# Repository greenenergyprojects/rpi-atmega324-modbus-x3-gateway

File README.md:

# rpi-atmega324-modbus-x3-gateway

This project implements a Modbus Gateway.  

The device is a gateway between Modbus-TCP (via TCP/IP on Raspberry) to Modbus-RTU (RS-485).
Modbus-TCP frames are send via the Raspberry UART interface (115200 Bit/s) to one microcontroller as Modbus-ASCII frame.
The microcontroller converts the Modbus-ASCII to Modbus-RTU frame and is handling all real time needs of the
Modbus-RTU standard. Frames for the other two Modbus interfaces are send via SPI interface to the second microcontroller.

**Features:**

* 3 interfaces Modbus-RTU
* 2 Microcontrollers (Atmgea324P)
* Raspberry PI
* For DIN-rail housing [Camdenboss CBRPP-DR-CLR](https://www.camdenboss.com/camden-boss/cbrpi-dr-2-3-clr-pi-b%2c-p2%2c-p3-din-rail-enclosure/c-23/p-16101)  
(W x H x D = 88mm x 90mm x 58mm; 4.8 DIN rails units)

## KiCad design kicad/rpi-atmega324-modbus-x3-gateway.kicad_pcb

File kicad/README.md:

# Manufacturing report

## Gerber Files

See [https://support.jlcpcb.com/article/44-how-to-export-kicad-pcb-to-gerber-files](https://support.jlcpcb.com/article/44-how-to-export-kicad-pcb-to-gerber-files)

# Bugs / Improvements

| Reference | Description |
| --------- | ----------- |
|           |             |

# Software

## Atmega324P Fuses

See [http://www.engbedded.com/fusecalc](http://www.engbedded.com/fusecalc)

* Ext crystal Osc, Frequ. 8.0- MHz, Startup 1K CK + 4.1ms
* Preserve EEPROM memory through Chip Erase cycle
* Serial program downloading enabled
* Brownout detection level 1.8V
* Watchdog disabled
* Boot flash size 1024 words, boot start 3c00 (=byte address 7800)
* Boot reset vector

```
avrdude -c usbasp -p atmega324p -U lfuse:w:0xfe:m -U hfuse:w:0xd2:m
avrdude -c usbasp -p atmega324p -U efuse:w:0xfe:m
```

## Bootloader

[https://www.htl-mechatronik.at/gitweb/public/sx/?p=Atmel-Bootloader.git;a=summary](https://www.htl-mechatronik.at/gitweb/public/sx/?p=Atmel-Bootloader.git;a=summary)

Download file [bootloader_atmega324p_115200_12MHz](https://www.htl-mechatronik.at/gitweb/public/sx/?p=Atmel-Bootloader.git;a=blob;f=bootloader_atmega324p/bootloader_atmega324p_115200_12MHz.hex)

avrdude -c usbasp -p atmega324p
avrdude -c usbasp -p atmega324p -e -U flash:w:bootloader_atmega324p_57600_12MHz.hex:i

## UART Baudrate

For the U1 microcontroller UART0 the baudrate 115200 Bit/s is recommended. This speed ensures a high data rate between RPI and microcontroller. Higher speeds are not possible with 12MHz system frequency.

Microcontroller: f = 12MHz		

|  Baudrate  |   Optimal UBRR0L  |     Error
|:----------:|:-----------------:| :-----------:
|     9600   |      155,25       |    0,0016
|    19200   |       77,12       |    0,0016
|    37400   |       39,11       |    0,0027
|    57600   |       25,04       |    0,0017
| **115200** |     **12,02**     |  **0,0017**
|   230400   |        5,51       |   -0,0888
|   560800   |        1,67       |   -0,1942

## Raspberry serial

Disable serial interface for Terminal with the tool `raspi-config`. Select `5 Interfacing Options` -> `P6 Serial` and select `NO`. Reboot is needed if the configuration has changed.

In the raspberry PI3 default configuration the Uart is used for Bluetooth communication. To allow serial port communcation via pin Txd (GPIO10) and Rxd (GPIO12)  a configuration change is necessary.

Edit the file`/boot/config.txt` and set the last lines to

```
enable_uart=1
core_freq=250
```

After reboot you can use `/dev/serial0` for serial communication between microcontroller and Raspberry. It depends on the raspberry version if `/dev/serial0` is a link to `/dev/ttyAMA0` (older raspberry) or `dev/ttyS0` (newer raspberry).

For more information:  
[http://www.netzmafia.de/skripten/hardware/RasPi/RasPi_Serial.html](http://www.netzmafia.de/skripten/hardware/RasPi/RasPi_Serial.html)

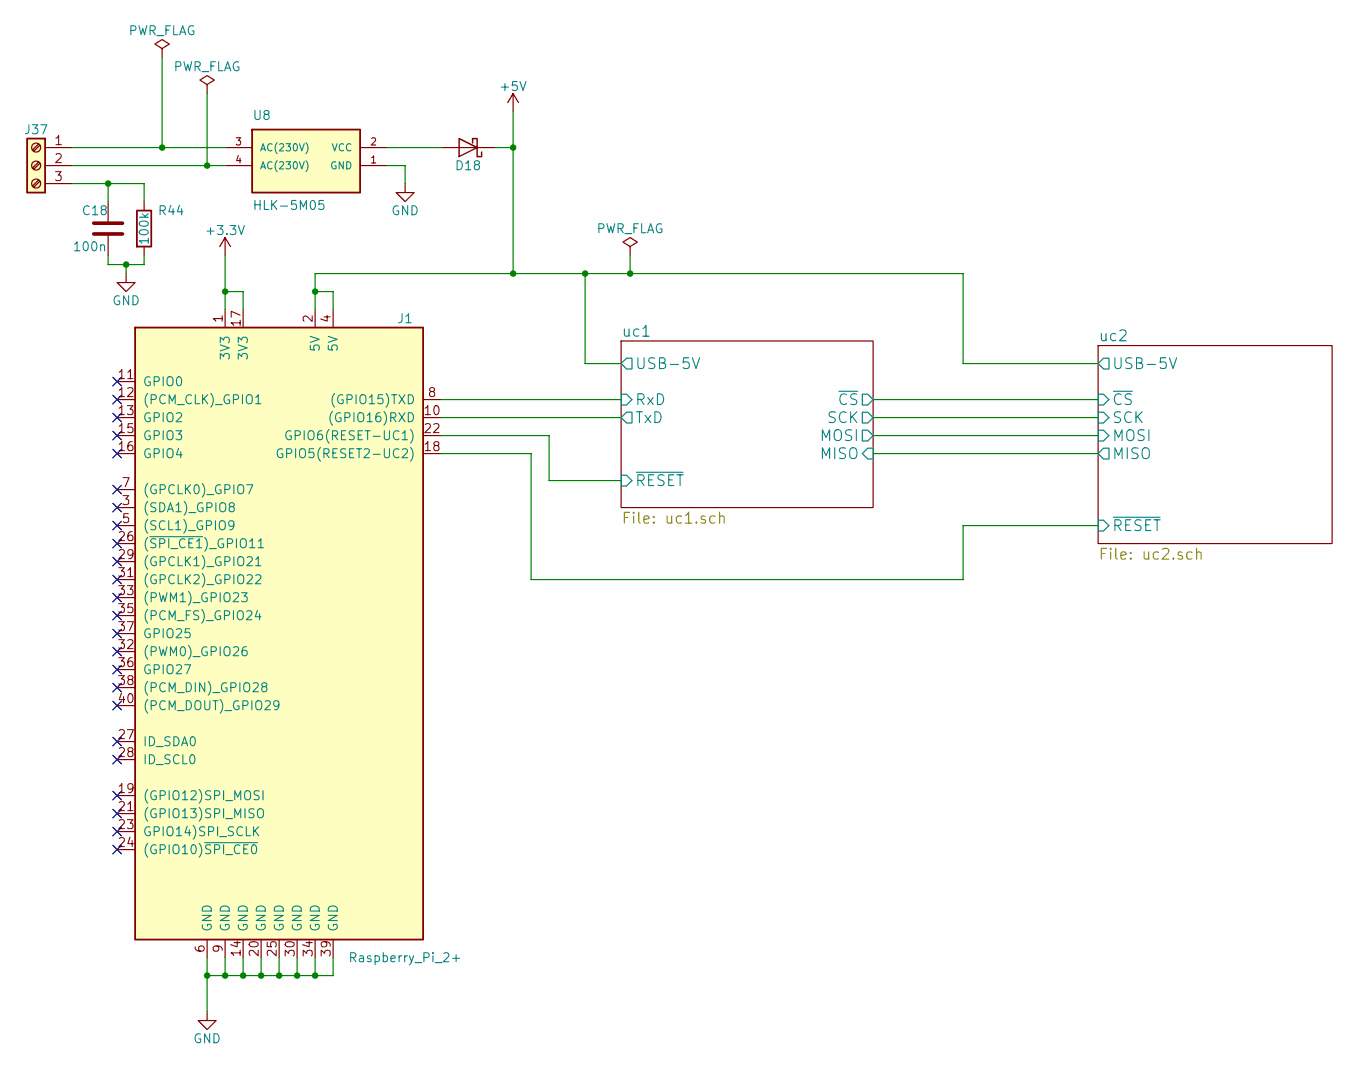
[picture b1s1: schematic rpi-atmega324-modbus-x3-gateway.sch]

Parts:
C18: 100n; C_1206_HandSoldering
D18: D_Schottky; D_2114
J1: Raspberry_Pi_2+; Raspberry-PI
J37: Screw_Terminal_01x03; Terminalblock-3x-5mm
R44: 100k; R_1206_HandSoldering
U8: HLK-5M05; HLK_5M05

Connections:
+3V3: J1.1 (3V3), J1.17 (3V3); also elsewhere on the board
+5V: D18.1 (K), J1.2 (5V), J1.4 (5V); also elsewhere on the board
/uc1/RxD: J1.8 ((GPIO15)TXD); also elsewhere on the board
/uc1/TxD: J1.10 ((GPIO16)RXD); also elsewhere on the board
/uc1/~RESET~: J1.22 (GPIO6(RESET-UC1)); also elsewhere on the board
/uc2/~RESET~: J1.18 (GPIO5(RESET2-UC2)); also elsewhere on the board
GND: C18.2, J1.6 (GND), J1.9 (GND), J1.14 (GND), J1.20 (GND), J1.25 (GND), J1.30 (GND), J1.34 (GND), J1.39 (GND), R44.2, U8.1 (GND); also elsewhere on the board
unnamed: C18.1, J37.3, R44.1
unnamed: D18.2 (A), U8.2 (VCC)
unnamed: J37.1, U8.3 (AC(230V))
unnamed: J37.2, U8.4 (AC(230V))

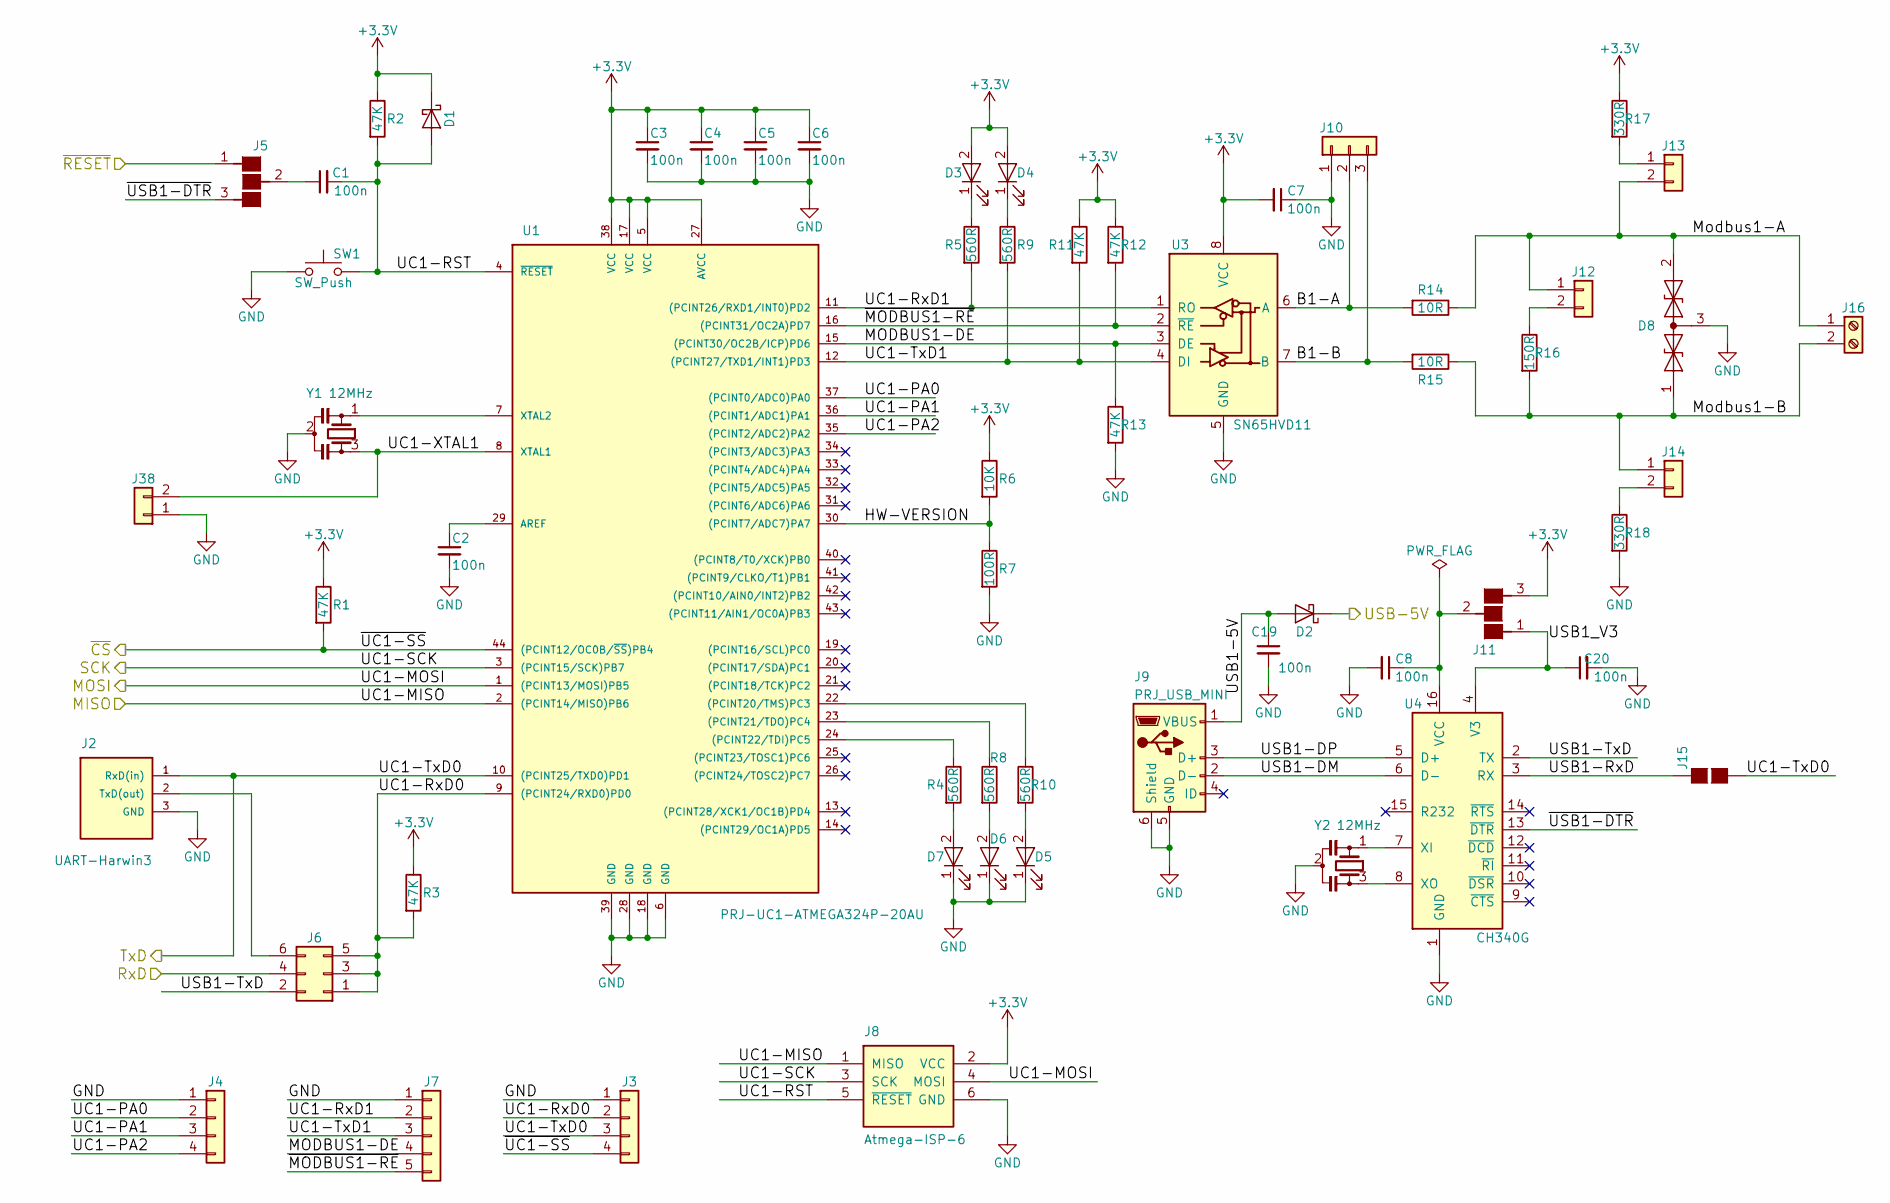
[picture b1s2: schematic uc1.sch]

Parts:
C1, C2, C3, C4, C5, C6, C7, C8, C19, C20: 100n; C_1206_HandSoldering
D1: D_Schottky; D_0805
D2: D_Schottky; D_2114
D3, D4, D5, D6, D7: LED; LED_0805_HandSoldering
D8: D_TVS_x2_AAC; SOT-23_Handsoldering
J2: UART-Harwin3; Harwin_LTek-Male_03x2.00mm_Straight_StrainRelief
J3, J4: Conn_01x04; Pin_Header_Straight_1x04_Pitch2.54mm
J5, J11: SOLDERBRDIGE-3; SOLDER-JUMPER_2-WAY
J6: Conn_02x03_Odd_Even; Pin_Header_Straight_2x03_Pitch2.54mm
J7: Conn_01x05; Pin_Header_Straight_1x05_Pitch2.54mm
J8: Atmega-ISP-6; Pin_Header_Straight_2x03_Pitch2.54mm
J9: PRJ_USB_MINI; USB_Mini-B-THT
J10: Conn_01x03; Pin_Header_Straight_1x03_Pitch2.54mm
J12, J13, J14, J38: Conn_01x02; Pin_Header_Straight_1x02_Pitch2.54mm
J15: SOLDERBRDIGE-2; SOLDER-JUMPER_1-WAY
J16: Screw_Terminal_01x02; Terminalblock-2x-5mm
R1, R2, R3, R11, R12, R13: 47K; R_1206_HandSoldering
R4, R5, R8, R9, R10: 560R; R_1206_HandSoldering
R6: 10K; R_1206_HandSoldering
R7: 100R; R_1206_HandSoldering
R14, R15: 10R; R_1206_HandSoldering
R16: 150R; R_1206_HandSoldering
R17, R18: 330R; R_1206_HandSoldering
SW1: SW_Push; SW_SPST_FSMSM
U1: PRJ-UC1-ATMEGA324P-20AU; TQFP-44_10x10mm_Pitch0.8mm_Handsolded
U3: SN65HVD11; SOIC-8_3.9x4.9mm_Pitch1.27mm_Handsolded
U4: CH340G; SOIC-16_3.9x9.9mm_Pitch1.27mm_HANDSOLDERED
Y1, Y2: 12MHz; Resonator-3pin_w7.0mm_h2.5mm

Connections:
+3V3: C3.1, C4.1, C5.1, C6.1, C7.2, D1.1 (K), D3.2 (A), D4.2 (A), J8.2 (VCC), J11.3 (G3), R1.1, R2.1, R3.1, R6.1, R11.1, R12.1, R17.1, U1.5 (VCC), U1.17 (VCC), U1.27 (AVCC), U1.38 (VCC), U3.8 (VCC); also elsewhere on the board
+5V: D2.1 (K); also elsewhere on the board
/uc1/B1-A: J10.2, R14.2, U3.6 (A)
/uc1/B1-B: J10.3, R15.2, U3.7 (B)
/uc1/HW-VERSION: R6.2, R7.1, U1.30 ((PCINT7/ADC7)PA7)
/uc1/MISO: J8.1 (MISO), U1.2 ((PCINT14/MISO)PB6); also elsewhere on the board
/uc1/MODBUS1-DE: J7.4, R13.1, U1.15 ((PCINT30/OC2B/ICP)PD6), U3.3 (DE)
/uc1/MOSI: J8.4 (MOSI), U1.1 ((PCINT13/MOSI)PB5); also elsewhere on the board
/uc1/Modbus1-A: D8.2 (A2), J12.1, J13.2, J16.1, R14.1
/uc1/Modbus1-B: D8.1 (A1), J14.1, J16.2, R15.1, R16.2
/uc1/RxD: J6.4; also elsewhere on the board
/uc1/SCK: J8.3 (SCK), U1.3 ((PCINT15/SCK)PB7); also elsewhere on the board
/uc1/TxD: J2.1 (RxD(in)), J3.3, J15.2 (G2), U1.10 ((PCINT25/TXD0)PD1); also elsewhere on the board
/uc1/UC1-PA0: J4.2, U1.37 ((PCINT0/ADC0)PA0)
/uc1/UC1-PA1: J4.3, U1.36 ((PCINT1/ADC1)PA1)
/uc1/UC1-PA2: J4.4, U1.35 ((PCINT2/ADC2)PA2)
/uc1/UC1-RST: C1.2, D1.2 (A), J8.5 (~RESET~), R2.2, SW1.2, U1.4 (~RESET)
/uc1/UC1-RxD0: J3.2, J6.1, J6.3, J6.5, R3.2, U1.9 ((PCINT24/RXD0)PD0)
/uc1/UC1-RxD1: J7.2, R5.2, U1.11 ((PCINT26/RXD1/INT0)PD2), U3.1 (RO)
/uc1/UC1-TxD1: J7.3, R9.2, R11.2, U1.12 ((PCINT27/TXD1/INT1)PD3), U3.4 (DI)
/uc1/UC1-XTAL1: J38.2, U1.8 (XTAL1), Y1.3
/uc1/USB1-5V: C19.1, D2.2 (A), J9.1 (VBUS)
/uc1/USB1-DM: J9.2 (D-), U4.6 (D-)
/uc1/USB1-DP: J9.3 (D+), U4.5 (D+)
/uc1/USB1-RxD: J15.1 (G1), U4.3 (RX)
/uc1/USB1-TxD: J6.2, U4.2 (TX)
/uc1/USB1_V3: C20.1, J11.1 (G1), U4.4 (V3)
/uc1/~CS~: J3.4, R1.2, U1.44 ((PCINT12/OC0B/~SS~)PB4); also elsewhere on the board
/uc1/~MODBUS1-RE~: J7.5, R12.2, U1.16 ((PCINT31/OC2A)PD7), U3.2 (~RE)
/uc1/~RESET~: J5.1 (G1); also elsewhere on the board
/uc1/~USB1-DTR~: J5.3 (G3), U4.13 (~DTR~)
GND: C2.2, C3.2, C4.2, C5.2, C6.2, C7.1, C8.2, C19.2, C20.2, D5.1 (K), D6.1 (K), D7.1 (K), D8.3 (common), J2.3 (GND), J3.1, J4.1, J7.1, J8.6 (GND), J9.5 (GND), J9.6 (Shield), J10.1, J38.1, R7.2, R13.2, R18.2, SW1.1, U1.6 (GND), U1.18 (GND), U1.28 (GND), U1.39 (GND), U3.5 (GND), U4.1 (GND), Y1.2, Y2.2; also elsewhere on the board
unnamed: C1.1, J5.2 (G2)
unnamed: C2.1, U1.29 (AREF)
unnamed: C8.1, J11.2 (G2), U4.16 (VCC)
unnamed: D3.1 (K), R5.1
unnamed: D4.1 (K), R9.1
unnamed: D5.2 (A), R10.2
unnamed: D6.2 (A), R8.2
unnamed: D7.2 (A), R4.2
unnamed: J2.2 (TxD(out)), J6.6
unnamed: J12.2, R16.1
unnamed: J13.1, R17.2
unnamed: J14.2, R18.1
unnamed: R4.1, U1.24 ((PCINT22/TDI)PC5)
unnamed: R8.1, U1.23 ((PCINT21/TDO)PC4)
unnamed: R10.1, U1.22 ((PCINT20/TMS)PC3)
unnamed: U1.7 (XTAL2), Y1.1
unnamed: U4.7 (XI), Y2.1
unnamed: U4.8 (XO), Y2.3

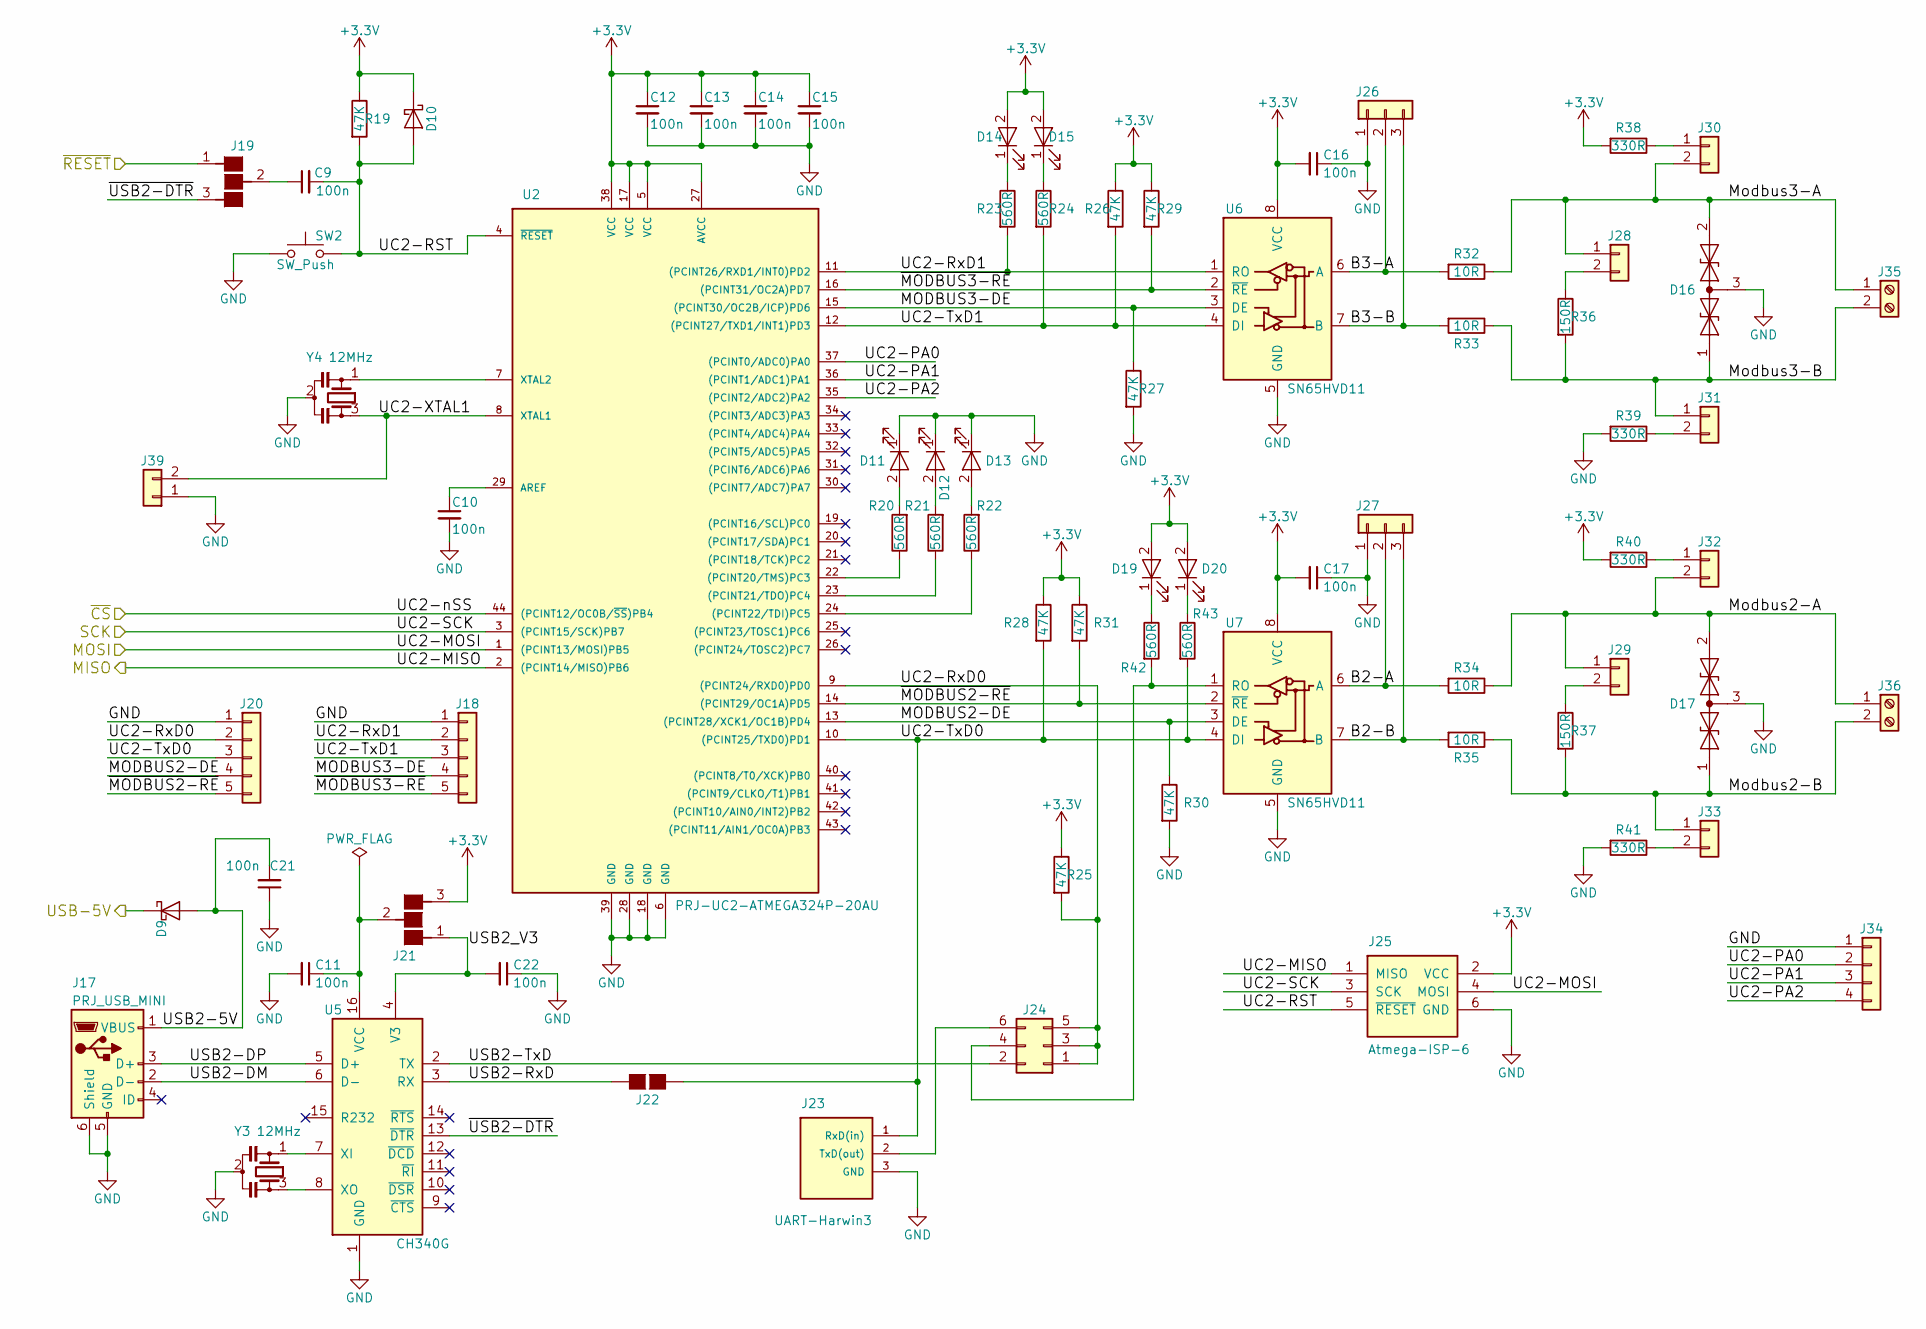
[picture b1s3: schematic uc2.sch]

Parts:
C9, C10, C11, C12, C13, C14, C15, C16, C17, C21, C22: 100n; C_1206_HandSoldering
D9: D_Schottky; D_2114
D10: D_Schottky; D_0805
D11, D12, D13, D14, D15, D19, D20: LED; LED_0805_HandSoldering
D16, D17: D_TVS_x2_AAC; SOT-23_Handsoldering
J17: PRJ_USB_MINI; USB_Mini-B-THT
J18, J20: Conn_01x05; Pin_Header_Straight_1x05_Pitch2.54mm
J19, J21: SOLDERBRDIGE-3; SOLDER-JUMPER_2-WAY
J22: SOLDERBRDIGE-2; SOLDER-JUMPER_1-WAY
J23: UART-Harwin3; Harwin_LTek-Male_03x2.00mm_Straight_StrainRelief
J24: Conn_02x03_Odd_Even; Pin_Header_Straight_2x03_Pitch2.54mm
J25: Atmega-ISP-6; Pin_Header_Straight_2x03_Pitch2.54mm
J26, J27: Conn_01x03; Pin_Header_Straight_1x03_Pitch2.54mm
J28, J29, J30, J31, J32, J33, J39: Conn_01x02; Pin_Header_Straight_1x02_Pitch2.54mm
J34: Conn_01x04; Pin_Header_Straight_1x04_Pitch2.54mm
J35, J36: Screw_Terminal_01x02; Terminalblock-2x-5mm
R19, R25, R26, R27, R28, R29, R30, R31: 47K; R_1206_HandSoldering
R20, R21, R22, R23, R24, R42, R43: 560R; R_1206_HandSoldering
R32, R33, R34, R35: 10R; R_1206_HandSoldering
R36, R37: 150R; R_1206_HandSoldering
R38, R39, R40, R41: 330R; R_1206_HandSoldering
SW2: SW_Push; SW_SPST_FSMSM
U2: PRJ-UC2-ATMEGA324P-20AU; TQFP-44_10x10mm_Pitch0.8mm_Handsolded
U5: CH340G; SOIC-16_3.9x9.9mm_Pitch1.27mm_HANDSOLDERED
U6, U7: SN65HVD11; SOIC-8_3.9x4.9mm_Pitch1.27mm_Handsolded
Y3, Y4: 12MHz; Resonator-3pin_w7.0mm_h2.5mm

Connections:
+3V3: C12.1, C13.1, C14.1, C15.1, C16.2, C17.2, D10.1 (K), D14.2 (A), D15.2 (A), D19.2 (A), D20.2 (A), J21.3 (G3), J25.2 (VCC), R19.1, R25.1, R26.1, R28.1, R29.1, R31.1, R38.2, R40.2, U2.5 (VCC), U2.17 (VCC), U2.27 (AVCC), U2.38 (VCC), U6.8 (VCC), U7.8 (VCC); also elsewhere on the board
+5V: D9.1 (K); also elsewhere on the board
/uc1/MISO: J25.1 (MISO), U2.2 ((PCINT14/MISO)PB6); also elsewhere on the board
/uc1/MOSI: J25.4 (MOSI), U2.1 ((PCINT13/MOSI)PB5); also elsewhere on the board
/uc1/SCK: J25.3 (SCK), U2.3 ((PCINT15/SCK)PB7); also elsewhere on the board
/uc1/~CS~: U2.44 ((PCINT12/OC0B/~SS~)PB4); also elsewhere on the board
/uc2/B2-A: J27.2, R34.2, U7.6 (A)
/uc2/B2-B: J27.3, R35.2, U7.7 (B)
/uc2/B3-A: J26.2, R32.2, U6.6 (A)
/uc2/B3-B: J26.3, R33.2, U6.7 (B)
/uc2/MODBUS2-DE: J20.4, R30.1, U2.13 ((PCINT28/XCK1/OC1B)PD4), U7.3 (DE)
/uc2/MODBUS3-DE: J18.4, R27.1, U2.15 ((PCINT30/OC2B/ICP)PD6), U6.3 (DE)
/uc2/Modbus2-A: D17.2 (A2), J29.1, J32.2, J36.1, R34.1
/uc2/Modbus2-B: D17.1 (A1), J33.1, J36.2, R35.1, R37.2
/uc2/Modbus3-A: D16.2 (A2), J28.1, J30.2, J35.1, R32.1
/uc2/Modbus3-B: D16.1 (A1), J31.1, J35.2, R33.1, R36.2
/uc2/UC2-PA0: J34.2, U2.37 ((PCINT0/ADC0)PA0)
/uc2/UC2-PA1: J34.3, U2.36 ((PCINT1/ADC1)PA1)
/uc2/UC2-PA2: J34.4, U2.35 ((PCINT2/ADC2)PA2)
/uc2/UC2-RST: C9.2, D10.2 (A), J25.5 (~RESET~), R19.2, SW2.2, U2.4 (~RESET)
/uc2/UC2-RxD0: J20.2, J24.1, J24.3, J24.5, R25.2, U2.9 ((PCINT24/RXD0)PD0)
/uc2/UC2-RxD1: J18.2, R23.2, U2.11 ((PCINT26/RXD1/INT0)PD2), U6.1 (RO)
/uc2/UC2-TxD0: J20.3, J22.1 (G1), J23.1 (RxD(in)), R28.2, R43.2, U2.10 ((PCINT25/TXD0)PD1), U7.4 (DI)
/uc2/UC2-TxD1: J18.3, R24.2, R26.2, U2.12 ((PCINT27/TXD1/INT1)PD3), U6.4 (DI)
/uc2/UC2-XTAL1: J39.2, U2.8 (XTAL1), Y4.3
/uc2/USB2-5V: C21.2, D9.2 (A), J17.1 (VBUS)
/uc2/USB2-DM: J17.2 (D-), U5.6 (D-)
/uc2/USB2-DP: J17.3 (D+), U5.5 (D+)
/uc2/USB2-RxD: J22.2 (G2), U5.3 (RX)
/uc2/USB2-TxD: J24.2, U5.2 (TX)
/uc2/USB2_V3: C22.2, J21.1 (G1), U5.4 (V3)
/uc2/~MODBUS2-RE~: J20.5, R31.2, U2.14 ((PCINT29/OC1A)PD5), U7.2 (~RE)
/uc2/~MODBUS3-RE~: J18.5, R29.2, U2.16 ((PCINT31/OC2A)PD7), U6.2 (~RE)
/uc2/~RESET~: J19.1 (G1); also elsewhere on the board
/uc2/~USB2-DTR~: J19.3 (G3), U5.13 (~DTR~)
GND: C10.2, C11.2, C12.2, C13.2, C14.2, C15.2, C16.1, C17.1, C21.1, C22.1, D11.1 (K), D12.1 (K), D13.1 (K), D16.3 (common), D17.3 (common), J17.5 (GND), J17.6 (Shield), J18.1, J20.1, J23.3 (GND), J25.6 (GND), J26.1, J27.1, J34.1, J39.1, R27.2, R30.2, R39.2, R41.2, SW2.1, U2.6 (GND), U2.18 (GND), U2.28 (GND), U2.39 (GND), U5.1 (GND), U6.5 (GND), U7.5 (GND), Y3.2, Y4.2; also elsewhere on the board
unnamed: C9.1, J19.2 (G2)
unnamed: C10.1, U2.29 (AREF)
unnamed: C11.1, J21.2 (G2), U5.16 (VCC)
unnamed: D11.2 (A), R20.2
unnamed: D12.2 (A), R21.2
unnamed: D13.2 (A), R22.2
unnamed: D14.1 (K), R23.1
unnamed: D15.1 (K), R24.1
unnamed: D19.1 (K), R42.1
unnamed: D20.1 (K), R43.1
unnamed: J23.2 (TxD(out)), J24.6
unnamed: J24.4, R42.2, U7.1 (RO)
unnamed: J28.2, R36.1
unnamed: J29.2, R37.1
unnamed: J30.1, R38.1
unnamed: J31.2, R39.1
unnamed: J32.1, R40.1
unnamed: J33.2, R41.1
unnamed: R20.1, U2.22 ((PCINT20/TMS)PC3)
unnamed: R21.1, U2.23 ((PCINT21/TDO)PC4)
unnamed: R22.1, U2.24 ((PCINT22/TDI)PC5)
unnamed: U2.7 (XTAL2), Y4.1
unnamed: U5.7 (XI), Y3.1
unnamed: U5.8 (XO), Y3.3

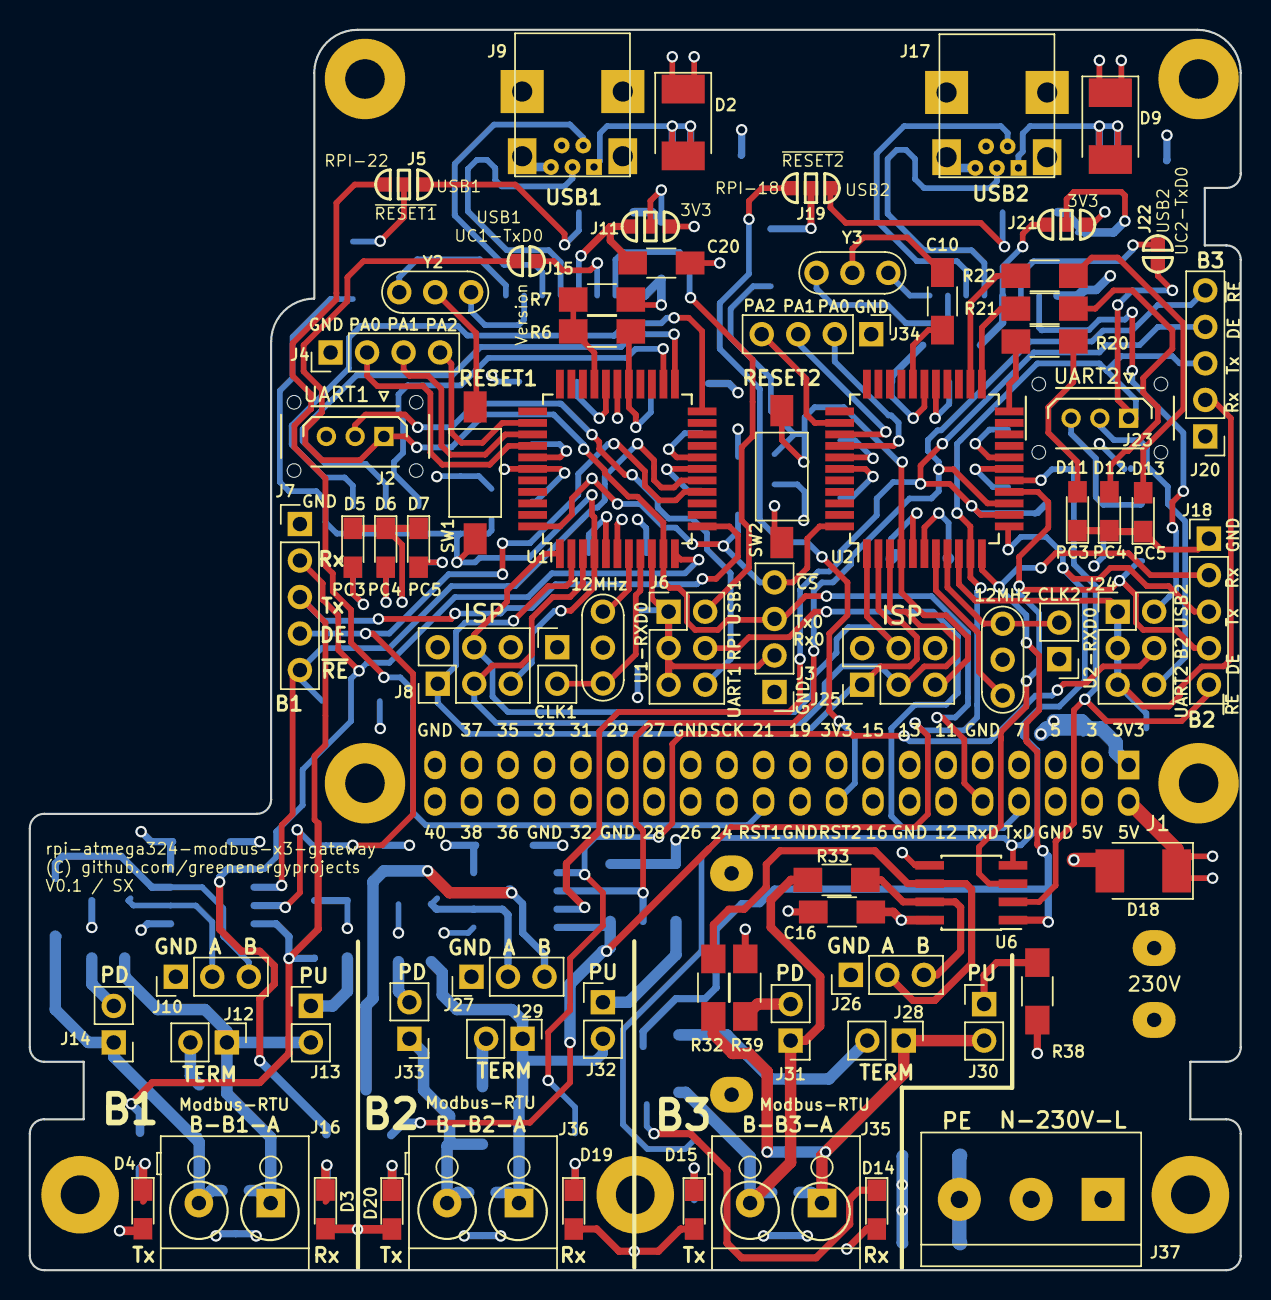
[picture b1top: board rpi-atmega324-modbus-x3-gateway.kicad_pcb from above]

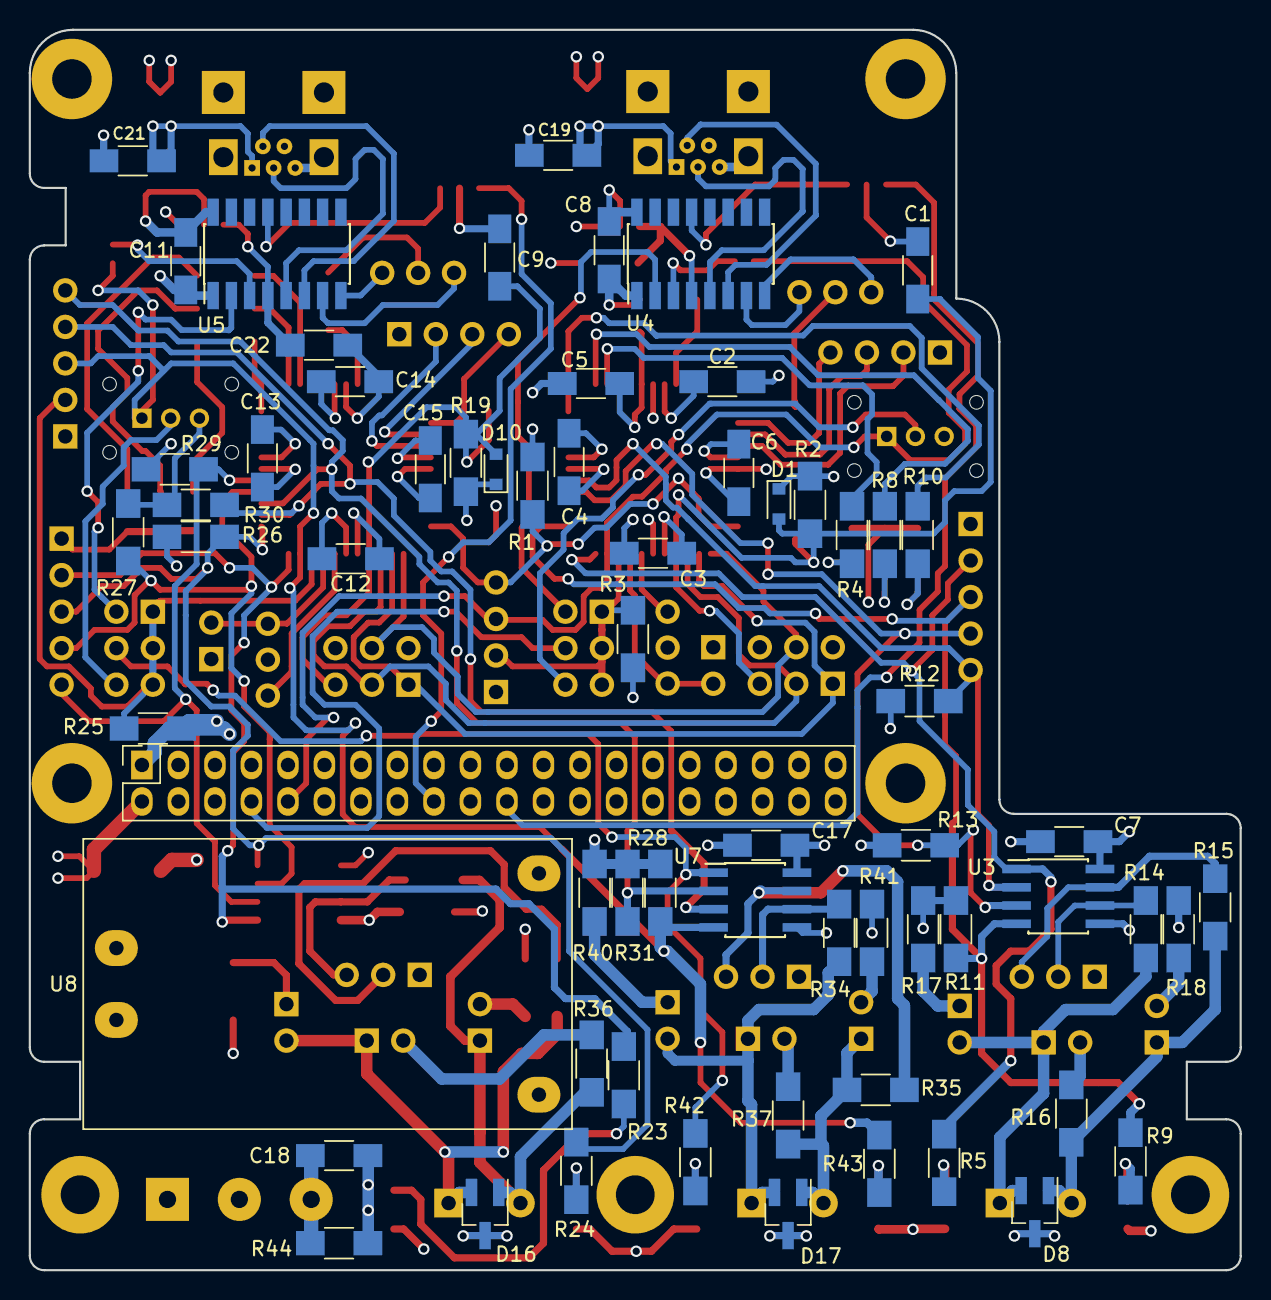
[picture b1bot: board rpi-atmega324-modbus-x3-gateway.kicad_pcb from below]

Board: 4 copper layers, 84.2 x 86.3 mm, 139 parts (64 on the bottom side), 107 nets.

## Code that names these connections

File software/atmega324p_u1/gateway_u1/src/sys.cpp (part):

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        DDRC = 0x38;    // LED D7,D8,D9
        PORTC |= 0x80;  // Pullup switch 2 (PC7)

        PORTD |= ((1 << PD7) | (1 << PD5));
        PORTD &= ~(1 << PD6);
        PORTD &= ~(1 << PD4);
        DDRD |= 0xf0;  // PD7=nRE1, PD6=DE1, PD5=nRE2, PD4=DE2

        // Timer 0 for task machine
        OCR0A  = (F_CPU + 4) / 8 / 10000 - 1;
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        // OCR1A = sys.modbus[0].dT1_35;

        // SPI Master
        DDRB  |= (1 << PB7) | (1 << PB5) | (1 << PB4);  // SCLK, MOSI, nSS
        PORTB |= (1 << PB4);
        // SPSR0 |= (1 << SPI2X0);
        SPCR0  = (1 << SPE0) | (1 << MSTR0) | (1 << SPIE0) | (1 << SPR00); //  | (1 << CPHA0) | (1 << CPOL0);
        PORTB &= ~(1 << PB4);
        SPDR0 = 0x00;
        
        // connect libc functions printf(), gets()... to UART
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
    void setLedGreen (uint8_t on) {
        if (on) {
            PORTC |= (1 << PC5);
        } else {
            PORTC &= ~(1 << PC5);
        }
    }

    void setLedYellow (uint8_t on) {
        if (on) {
            PORTC |= (1 << PC4);
        } else {
            PORTC &= ~(1 << PC4);
        }
    }

    void setLedRed (uint8_t on) {
        if (on) {
            PORTC |= (1 << PC3);
        } else {
            PORTC &= ~(1 << PC3);
        }
    }

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    }

    void toggleLedGreen () {
        PORTC ^= (1 << PC5);
    }

    void toggleLedYellow () {
        PORTC ^= (1 << PC4);
    }

    void toggleLedRed () {
        PORTC ^= (1 << PC3);
    }

    void togglePortA (uint8_t index) {
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        sys.uart1Buf = buf;
        sys.uart1Size = size - 1;
        UCSR1B = (1 << TXCIE1) | (1 << TXEN1); // no |= otherwise echo received !!
        PORTD |= (1 << PD6); // MODBUS1-DE = 1
        PORTD |= (1 << PD7); // MODBUS1-nRE = 1
        UDR1 = *sys.uart1Buf++;
    }

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        UDR1 = *uc1_sys::sys.uart1Buf++;
        uc1_sys::sys.uart1Size--;
    } else {
        PORTD &= ~(1 << PD6); // MODBUS1-DE = 0
        PORTD &= ~(1 << PD7); // MODBUS1-nRE = 0
        UCSR1B |= (1 << RXCIE1) | (1 << RXEN1);
        UCSR1B &= ~((1 << TXCIE1) | (1 << TXEN1));
        uc1_app::uart1ReadyToSent(0);
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
ISR (SPI_STC_vect) {
    static uint8_t b = 0;
    uint8_t cs = (PORTB & (1 << PB4));
    if (cs) {
        PORTB &= ~(1 << PB4);    
        SPDR0 = b;
    } else {
        PORTB |= (1 << PB4); 
        b = SPDR0;
        b = uc1_app::handleSpiByte(b);
        SPDR0 = 0;
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
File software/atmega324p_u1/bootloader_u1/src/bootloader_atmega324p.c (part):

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
void setLedGreen (int8_t on) {
    if (on < 0) {
        PORTC ^= (1 << PC5);
    } else if (on > 0) {
        PORTC |= (1 << PC5);
    } else {
        PORTC &= (1 << PC5);
    }
}

void setLedYellow (int8_t on) {
    if (on < 0) {
        PORTC ^= (1 << PC4);
    } else if (on > 0) {
        PORTC |= (1 << PC4);
    } else {
        PORTC &= (1 << PC4);
    }
}

void setLedRed (int8_t on) {
    if (on < 0) {
        PORTC ^= (1 << PC3);
    } else if (on > 0) {
        PORTC |= (1 << PC3);
    } else {
        PORTC &= (1 << PC3);
    }
}

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    while (len > 0) {
        len--;
        uint8_t b = *pb++;
        PORTA ^= (1 << PA0);
        sendSpiByte(b);
        
        volatile int16_t timer = 0x100;
        while (timer > 0) {
            cli();
            if (spi.received != 0) {
                PORTA ^= (1 << PA1);
                if (b != spi.received) {
                    sei();
                    return 1; // status 1 - SPI communication error
                }
                if (len <= 1) {
                    spi.skipUart = 0;
                    PORTA ^= (1 << PA2);                                        
                }
                spi.received = 0;
                timer = 0;
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            sendUartByte(spi.received);
        }
    }
    PORTB |= (1 << PB4); 
    spi.toSendShadow = spi.toSend;
    PORTB &= ~(1 << PB4);
    SPDR0 = spi.toSendShadow;
    spi.toSend = 0x00;
}
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

    // SPI f = fcpu / 4 = 3MHz@12MHz
    DDRB  |= (1 << PB7) | (1 << PB5) | (1 << PB4);  // SCLK, MOSI, nSS
    PORTB |= (1 << PB4);
    // SPSR0 |= (1 << SPI2X0);
    
    
    SPCR0  = (1 << SPE0) | (1 << MSTR0) | (1 << SPIE0) | (1 << SPR10);
    PORTB |= (1 << PB4); 
    
    MCUCR = (1 << IVCE);
    MCUCR = (1 << IVSEL); 
    
    sei();
    PORTB &= ~(1 << PB4);
    SPDR0 = 0x00;

    sendLineFeed();
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
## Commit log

2018-09-17 PCB design V0.1 complete routed
2018-09-20 PCB V0.1 Tapeout
2018-10-07 Update dist/README.md (first print manufactured)
2018-10-28 Bootloader u1 worling with flashuc
2018-12-17 create new project with authentication
2019-01-06 First running version on new system
2019-01-27 new statistics with second cluster process
2019-02-08 new statistics
2019-03-07 bugfix nibe1155 energy
2019-03-16 Archive now ready
2019-04-07 bootloader buggy but working
2019-04-08 bootloader for U2 V1.00
2019-04-16 uCSim first running...
2019-04-23 uCSim B1 ready
2019-06-01 ok in simulation
2019-06-09 Bugfix Homecontrol V1.6
2019-07-06 V1.6.1 Bugfix
2019-07-30 U1 Testsoftware for INV500
2019-10-04 apparent power/phase power/phase voltage added
2019-10-04 update ngx/overview
2019-10-05 ngx overview changes
2019-10-13 overview update
2019-10-13 statistics update (bat e in/out)
2019-10-14 bugfix statistics
2020-03-05 V1.9.0 (fronius meter defect
2020-11-06 V1.10.1, add boiler parameter batpMinLoad
2020-11-07 V1.10.2 - hot water boiler improvements
